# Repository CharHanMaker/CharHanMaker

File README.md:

# 🍚CharHan!!

チャーハンの調理を自動化するCharHan!!というロボットを作りました。

[CharHan!!-YouTube](https://www.youtube.com/watch?v=2m1POazWTIs)

## 🔥CharHan!!機械概要

案2を採用しました。

左右にモータを取り付けて左右の回転の同期する制御を入れています。

左右のリンクにエンコーダを搭載しており、角度と速度を左右で同期しています。

制御器は3種類設計し、評価しました。

## 🤖炒め作業の自動化

このようなチャーハンファームを作ることで省人化できるのではないかと思っております。

## 📁ファイルに関して

- Program
  - ロボットを動かすソフトウェアが入っています。PlatformIOで開発を行いました。
  - SystemIdentificationDataにMATLABでシステム同定を行ったプログラムが入っています。
    - 以下がシステム同定を行うために使用した組み込み側のデータロギングのプログラムです。シリアルモニターで受け取った文字列を元にCSVで書き出して整形してシステム同定を行いました。
    - `Program/main_tomix/src/Modes/SystemIdentification2`
    - `Program/main_tomix/src/Modes/SystemIdentification2`
- PCB
  - 基板データが入っています。KiCad7で開発しました。
- Image
  - README.mdの画像が入っています。

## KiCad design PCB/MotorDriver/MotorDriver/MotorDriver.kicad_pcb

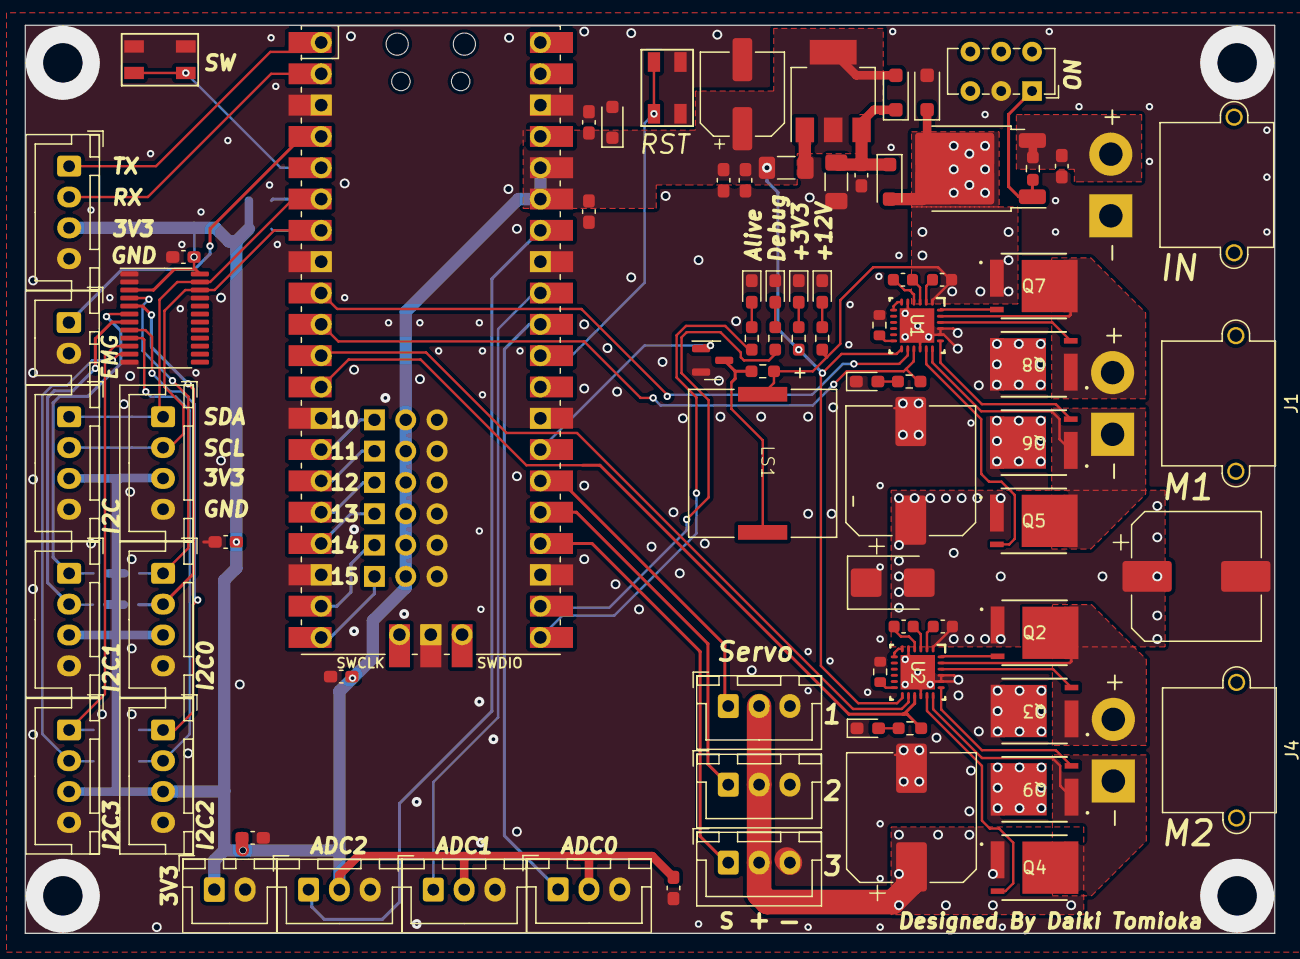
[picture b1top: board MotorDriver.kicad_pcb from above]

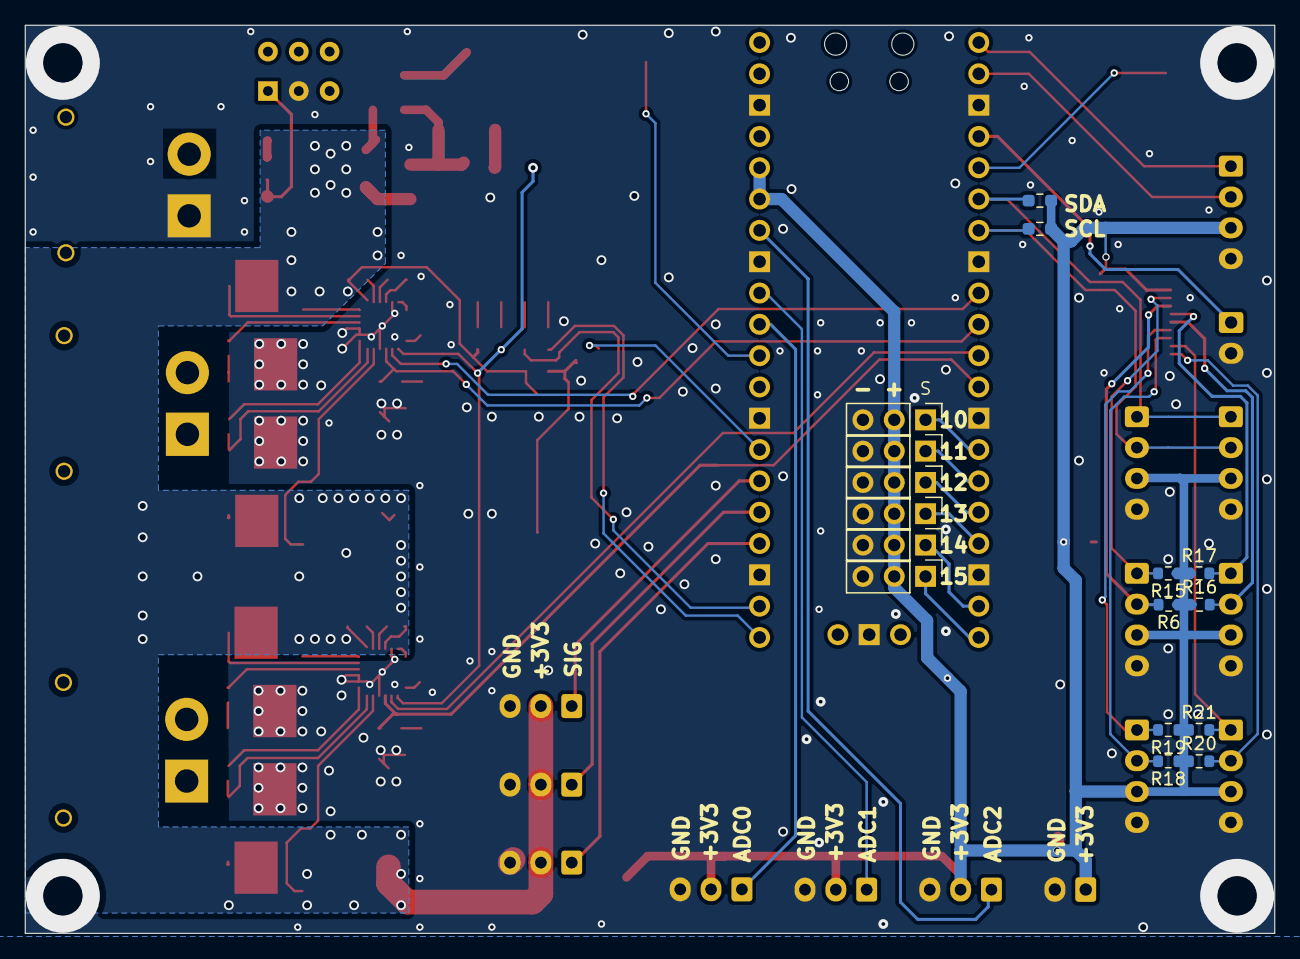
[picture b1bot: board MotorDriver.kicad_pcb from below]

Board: 2 copper layers, 101.3 x 73.7 mm, 95 parts (16 on the bottom side), 69 nets.

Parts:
C1, C17: 0.1u; C_0603_1608Metric
C2, C12: 1u; C_0603_1608Metric
C3, C11, C21: 220u; CP_Elec_10x10
C4, C5, C8, C9, C10, C13, C15, C16, C18, C19, C20: 0.1u; C_0603_1608Metric_Pad1.08x0.95mm_HandSolder
C6, C7: 22u; C_1206_3216Metric_Pad1.33x1.80mm_HandSolder
C14: 220u; CP_Elec_6.3x5.4
D1, D2, D10: ＧＳ１０１０ＦＬ; D_SOD-123F
D3: 3.3V; D_SOD-323_HandSoldering
D4, D5, D6, D7, D8, D9: LED; LED_0603_1608Metric_Pad1.05x0.95mm_HandSolder
J1, J3, J4: XT30PW-M; AMASS_XT30PW-M_1x02_P2.50mm_Horizontal
J2, J5, J9, J10, J13, J15: JST-XH; JST_XH_B3B-XH-A_1x03_P2.50mm_Vertical
J6, J24: JST-XH; JST_XH_B2B-XH-A_1x02_P2.50mm_Vertical
J7, J8, J11, J12, J14, J17, J18: JST-XH; JST_XH_B4B-XH-A_1x04_P2.50mm_Vertical
J16, J19, J20, J21, J22, J23: JST-XH; PinHeader_1x03_P2.54mm_Vertical
LS1: PKLCS1212E4001-R1; PKL
Q1: TJ60S04M3L; TO-252-2
Q2, Q3, Q4, Q5, Q6, Q7, Q8, Q9: NMOS; TPH11006NL_SOP Advance_TOS-M
Q10: NMOS; SOT-23
R1, R3: 10k; R_0603_1608Metric
R2, R5, R7, R8, R14: 10k; R_0603_1608Metric_Pad0.98x0.95mm_HandSolder
R6, R15, R16, R17, R18, R19, R20, R21: 4.7k; R_0603_1608Metric
R9, R10, R11, R12, R13: 1k; R_0603_1608Metric_Pad0.98x0.95mm_HandSolder
SW1: SW_DPST_x2; SW_E-Switch_EG1271_SPDT
SW2, SW3: SW_Push; SKRPACE010
TVS1: 12V; D_SMB
U1, U2: DRV8701ERGET; DRV8701ERGET_NV
U3: TCA9548APWR; TSSOP-24_4.4x7.8mm_P0.65mm
U4: Pico; RPi_Pico_SMD_TH
U5: AZ1117CH-3.3TR; SOT-223-3_TabPin2

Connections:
+3V3: C7.1, C8.1, C9.1, C10.1, C13.1, C14.1, C15.1, C16.1, C18.1, C19.1, C20.1, D3.1 (K), D10.2 (A), J7.3, J8.3, J10.2, J11.3, J12.3, J13.2, J14.3, J15.2, J16.2, J17.3, J18.3, J19.2, J20.2, J21.2, J22.2, J23.2, J24.1, R6.1, R7.1, R9.1, R14.1, R15.1, R16.1, R17.1, R18.1, R19.1, R20.1, R21.1, U1.13 (SLEEP_N), U2.13 (SLEEP_N), U3.3 (~RESET), U3.24 (VCC), U4.35 (ADC_VREF), U4.36 (3V3), U5.2 (OUTPUT)
+12V: C2.1, C3.1, C11.1, C12.1, C21.1, D1.2 (A), D2.1 (K), J2.2, J5.2, J9.2, LS1.P, Q1.2 (D), Q2.1 (D), Q4.1 (D), Q5.1 (D), Q7.1 (D), R5.1, R8.1, TVS1.2 (A), U1.1 (VM), U2.1 (VM)
+BATT: C4.2, J3.2, Q1.3 (S), R2.1
/12VIN: C5.1, C6.1, D1.1 (K), D10.1 (K), U5.3 (INPUT)
/MotorDriveUnit1/AVDD: U2.6 (VREF), U2.7 (AVDD)
/MotorDriveUnit/AVDD: U1.6 (VREF), U1.7 (AVDD)
ADC0: J10.1, U4.31 (GPIO26_ADC0)
ADC1: J13.1, U4.32 (GPIO27_ADC1)
ADC2: J15.1, U4.34 (GPIO28_ADC2)
Alive_LED: R13.1, U4.22 (GPIO17)
BUZZER: Q10.2 (G), U4.27 (GPIO21)
Debug_LED: R12.1, U4.21 (GPIO16)
EMG: J6.1, U4.4 (GPIO2)
GND: C3.2, C4.1, C5.2, C6.2, C7.2, C8.2, C9.2, C10.2, C11.2, C13.2, C14.2, C15.2, C16.2, C18.2, C19.2, C20.2, C21.2, D2.2 (A), D3.2 (A), D4.1 (K), D5.1 (K), D6.1 (K), D7.1 (K), D8.1 (K), D9.1 (K), J2.3, J3.1, J5.3, J6.2, J7.4, J8.4, J9.3, J10.3, J11.4, J12.4, J13.3, J14.4, J15.3, J16.3, J17.4, J18.4, J19.3, J20.3, J21.3, J22.3, J23.3, J24.2, Q3.3 (S), Q6.3 (S), Q8.3 (S), Q9.3 (S), Q10.3 (S), R1.1, R3.1, SW1.2 (B), SW2.1, SW3.1, TVS1.1 (K), U1.5 (GND), U1.16 (GND), U1.20 (SN), U1.21 (SP), U1.25 (PAD), U2.5 (GND), U2.16 (GND), U2.20 (SN), U2.21 (SP), U2.25 (PAD), U3.1 (A0), U3.2 (A1), U3.12 (GND), U3.21 (A2), U4.3 (GND), U4.8 (GND), U4.13 (GND), U4.18 (GND), U4.23 (GND), U4.28 (GND), U4.33 (AGND), U4.38 (GND), U4.42 (GND), U5.1 (GND)
GPIO10: J16.1, U4.14 (GPIO10)
GPIO11: J19.1, U4.15 (GPIO11)
GPIO12: J20.1, U4.16 (GPIO12)
GPIO13: J21.1, U4.17 (GPIO13)
GPIO14: J22.1, U4.19 (GPIO14)
GPIO15: J23.1, U4.20 (GPIO15)
INA1: R10.1, U1.15 (PH_IN1), U4.10 (GPIO7)
INA2: U1.14 (EN_IN2), U4.9 (GPIO6)
INB1: R11.1, U2.15 (PH_IN1), U4.12 (GPIO9)
INB2: U2.14 (EN_IN2), U4.11 (GPIO8)
Motor1A: J1.1, Q5.3 (S), Q6.1 (D), U1.18 (SH1)
Motor1B: J1.2, Q7.3 (S), Q8.1 (D), U1.23 (SH2)
Motor2A: J4.1, Q4.3 (S), Q9.1 (D), U2.18 (SH1)
Motor2B: J4.2, Q2.3 (S), Q3.1 (D), U2.23 (SH2)
unnamed: D4.2 (A), R8.2
unnamed: D5.2 (A), R9.2
unnamed: D6.2 (A), R10.2
unnamed: D7.2 (A), R11.2
unnamed: D8.2 (A), R12.2
unnamed: D9.2 (A), R13.2
unnamed: Q1.1 (G), R2.2, SW1.1 (A)
unnamed: Q2.2 (G), U2.24 (GH2)
unnamed: Q3.2 (G), U2.22 (GL2)
unnamed: Q4.2 (G), U2.17 (GH1)
unnamed: Q5.2 (G), U1.17 (GH1)
unnamed: Q6.2 (G), U1.19 (GL1)
unnamed: Q7.2 (G), U1.24 (GH2)
unnamed: Q8.2 (G), U1.22 (GL2)
unnamed: Q9.2 (G), U2.19 (GL1)
unnamed: LS1.N, Q10.1 (D), R5.2
unnamed: C1.1, U1.3 (CPH)
unnamed: C1.2, U1.4 (CPL)
unnamed: R1.2, U1.12 (IDRIVE)
unnamed: C2.2, U1.2 (VCP)
unnamed: C17.1, U2.3 (CPH)
unnamed: C17.2, U2.4 (CPL)
unnamed: R3.2, U2.12 (IDRIVE)
unnamed: C12.2, U2.2 (VCP)
RUN: SW3.2, U4.30 (RUN)
RX0: J17.2, U4.2 (GPIO1)
SCL: J8.2, J11.2, R14.2, U3.22 (SCL), U4.7 (GPIO5)
SCL0: J7.2, R6.2, U3.5 (SC0)
SCL1: J12.2, R16.2, U3.7 (SC1)
SCL2: J14.2, R18.2, U3.9 (SC2)
SCL3: J18.2, R20.2, U3.11 (SC3)
SDA: J8.1, J11.1, R7.2, U3.23 (SDA), U4.6 (GPIO4)
SDA0: J7.1, R15.2, U3.4 (SD0)
SDA1: J12.1, R17.2, U3.6 (SD1)
SDA2: J14.1, R19.2, U3.8 (SD2)
SDA3: J18.1, R21.2, U3.10 (SD3)
SW: SW2.2, U4.5 (GPIO3)
Servo1: J9.1, U4.24 (GPIO18)
Servo2: J2.1, U4.25 (GPIO19)
Servo3: J5.1, U4.26 (GPIO20)
TX0: J17.1, U4.1 (GPIO0)

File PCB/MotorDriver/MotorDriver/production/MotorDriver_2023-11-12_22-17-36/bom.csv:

Designator,Footprint,Quantity,Value,LCSC Part #
"C1, C10, C13, C15, C16, C17, C18, C19, C20, C4, C5, C8, C9",0603,13,0.1u,
"C11, C21, C3",CP_Elec_10x10,3,220u,
"C12, C2",0603,2,1u,
C14,CP_Elec_6.3x5.4,1,220u,
"C6, C7",1206,2,22u,
D1,D_SOD-123F,1,ＧＳ１０１０ＦＬ,
D3,D_SOD-323_HandSoldering,1,D_Schottky,
"D4, D5, D6, D7, D8, D9",0603,6,LED,
"J1, J3, J4",AMASS_XT30PW-M_1x02_P2.50mm_Horizontal,3,XT30PW-M,
"J10, J13, J15, J2, J5, J9",JST_XH_B3B-XH-A_1x03_P2.50mm_Vertical,6,JST-XH,
"J11, J12, J14, J17, J18, J7, J8",JST_XH_B4B-XH-A_1x04_P2.50mm_Vertical,7,JST-XH,
"J16, J19, J20, J21, J22, J23",PinHeader_1x03_P2.54mm_Vertical,6,JST-XH,
"J24, J6",JST_XH_B2B-XH-A_1x02_P2.50mm_Vertical,2,JST-XH,
LS1,PKL,1,PKLCS1212E4001-R1,
Q1,TO-252-2,1,TJ60S04M3L,
Q10,SOT-23,1,NMOS,
"Q2, Q3, Q4, Q5, Q6, Q7, Q8, Q9",TPH11006NL_SOP Advance_TOS-M,8,NMOS,
"R1, R14, R2, R3, R5, R7, R8",0603,7,10k,
"R10, R11, R12, R13, R9",0603,5,1k,
"R15, R16, R17, R18, R19, R20, R21, R6",0603,8,4.7k,
SW1,SW_E-Switch_EG1271_SPDT,1,SW_DPST_x2,
"SW2, SW3",SKRPACE010,2,SW_Push,
"U1, U2",DRV8701ERGET_NV,2,DRV8701ERGET,
U3,TSSOP-24_4.4x7.8mm_P0.65mm,1,TCA9548APWR,
U4,RPi_Pico_SMD_TH,1,Pico,
U5,SOT-223-3_TabPin2,1,AZ1117CH-3.3TR,

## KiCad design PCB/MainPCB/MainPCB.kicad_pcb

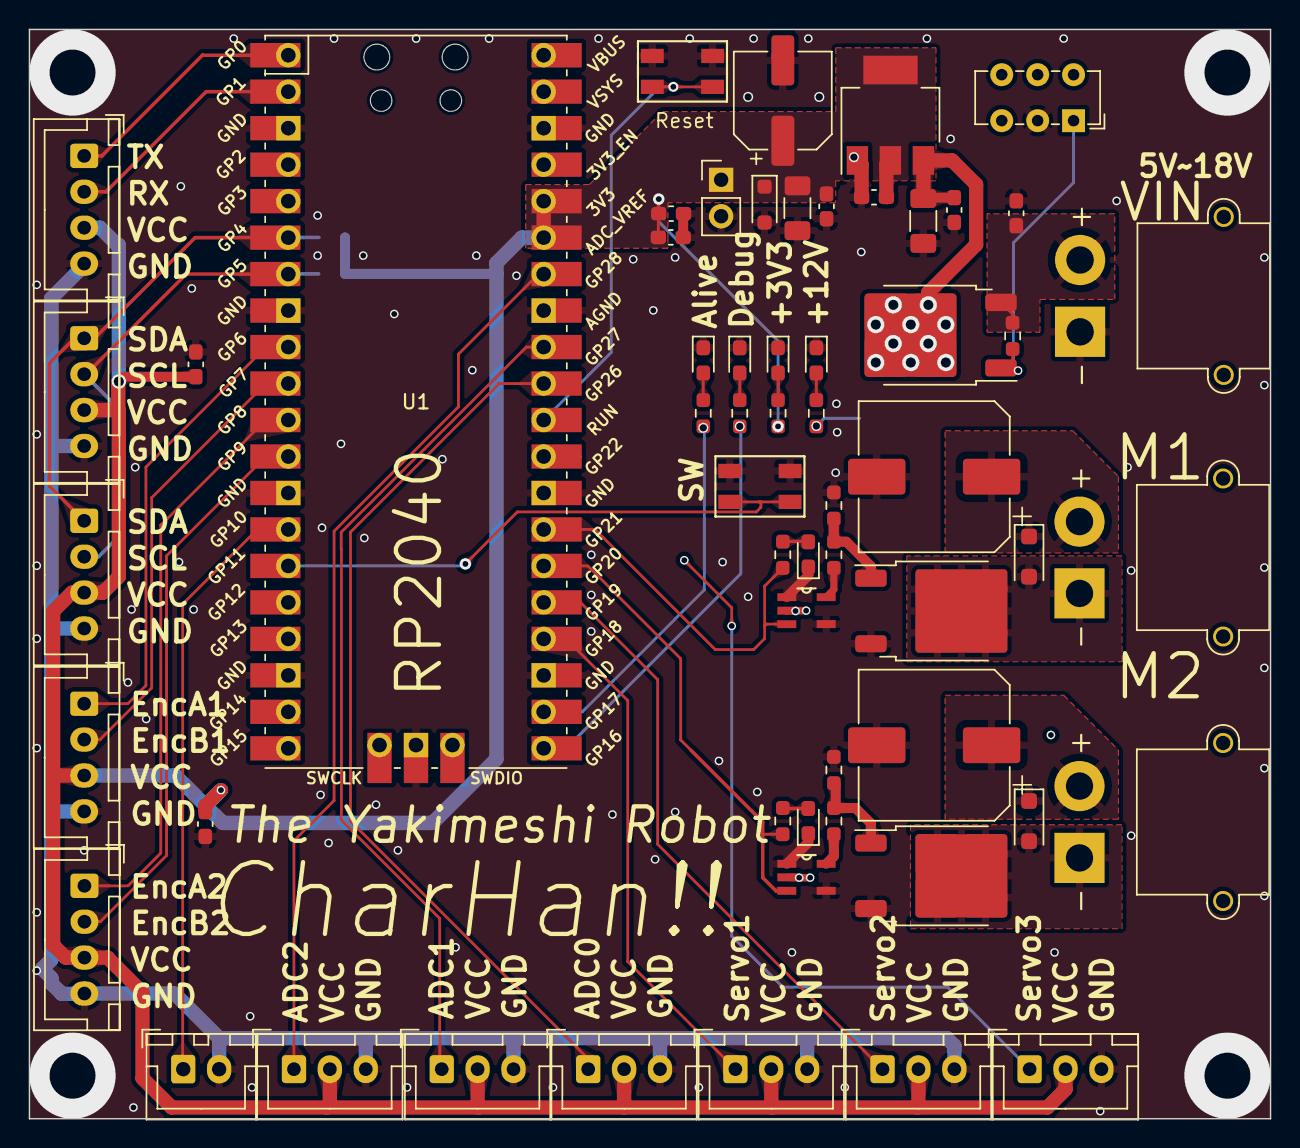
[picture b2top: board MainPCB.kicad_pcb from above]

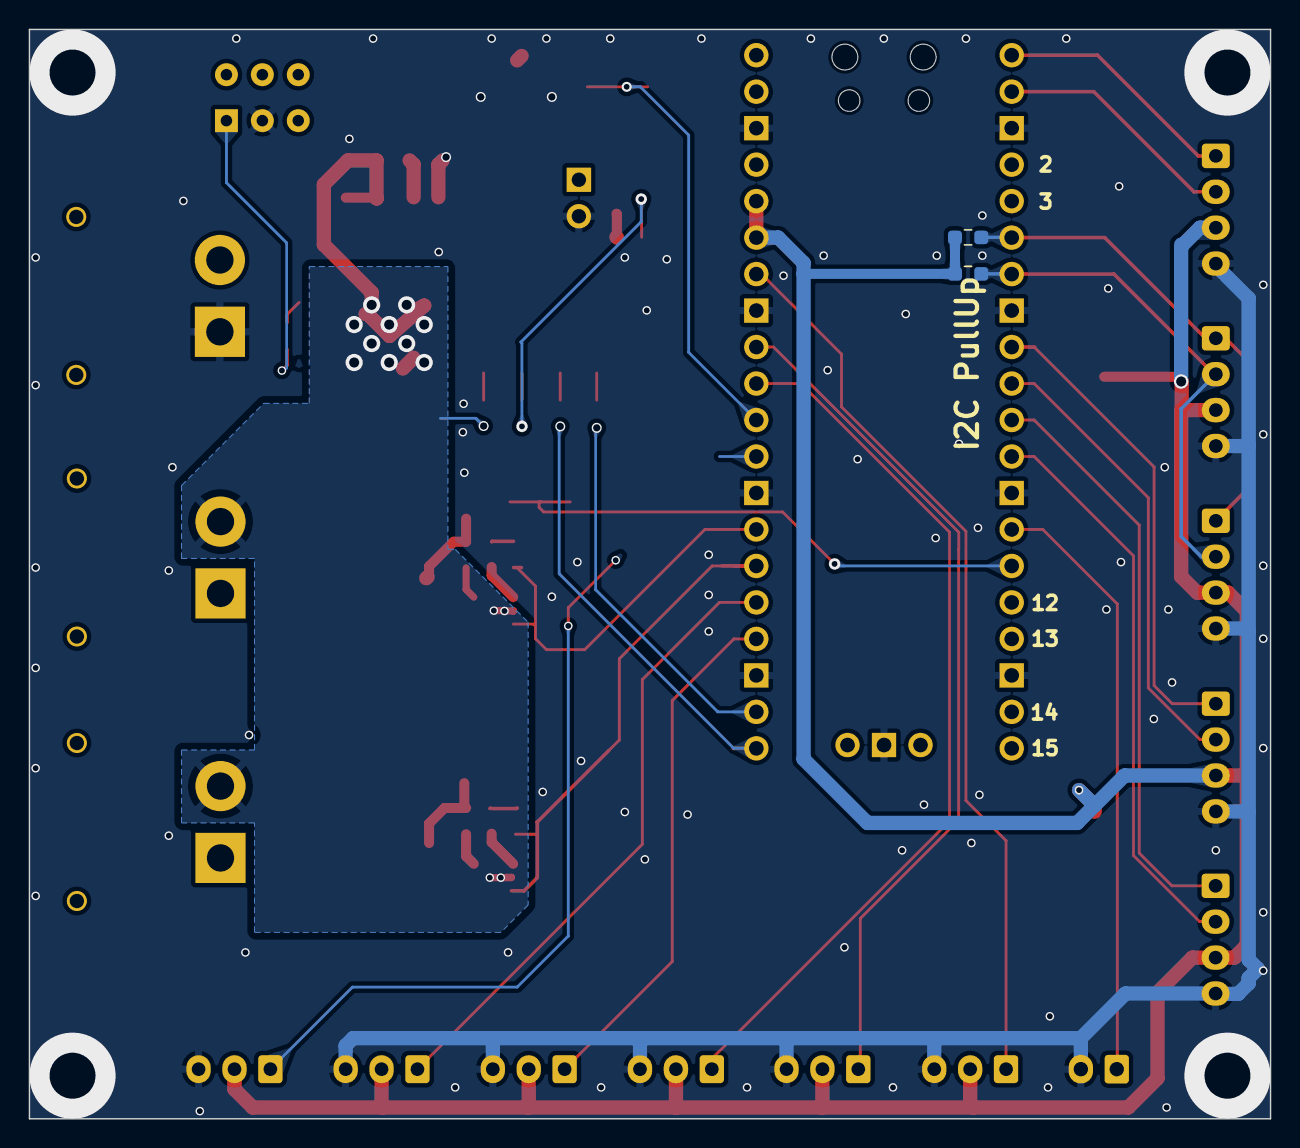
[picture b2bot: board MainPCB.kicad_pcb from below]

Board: 2 copper layers, 86.4 x 75.8 mm, 61 parts (2 on the bottom side), 38 nets.

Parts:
C2, C4: 220u; CP_Elec_10x10
C5, C6: 22u; C_1206_3216Metric_Pad1.33x1.80mm_HandSolder
C7, C9, C10, C11, C12, C13, C14, C15: 0.1u; C_0603_1608Metric_Pad1.08x0.95mm_HandSolder
C8: 220u; CP_Elec_6.3x5.4
D1: D_Schottky; D_SOD-323_HandSoldering
D2, D3, D4, D5, D6, D7: LED; LED_0603_1608Metric_Pad1.05x0.95mm_HandSolder
D8: ＧＳ１０１０ＦＬ; D_SOD-123F
D9: D; D_SOD-123F
J1, J12, J16: XT30PW-M; AMASS_XT30PW-M_1x02_P2.50mm_Horizontal
J2, J8, J9, J10, J11: JST-XH; JST_XH_B4B-XH-A_1x04_P2.50mm_Vertical
J3, J5, J6, J7, J14, J15: JST-XH; JST_XH_B3B-XH-A_1x03_P2.50mm_Vertical
J4: PinHeader_1x02_P2.54mm_Vertical
J13: JST-XH; JST_XH_B2B-XH-A_1x02_P2.50mm_Vertical
Q1, Q2: MTB7D0N6RJ3; TO-252-2
Q3: TJ60S04M3L; TO-252-2
R1, R2, R6, R7, R9: 1k; R_0603_1608Metric_Pad0.98x0.95mm_HandSolder
R3, R4, R5, R8, R10, R13: 10k; R_0603_1608Metric_Pad0.98x0.95mm_HandSolder
R11, R12: 51; R_0603_1608Metric_Pad0.98x0.95mm_HandSolder
SW1, SW3: SW_Push; SKRPACE010
SW2: SW_DPST_x2; SW_E-Switch_EG1271_SPDT
U1: Pico; RPi_Pico_SMD_TH
U2, U3: MCP1401T-E_OT; SOT95P270X145-5N
U4: AZ1117CH-3.3TR; SOT-223-3_TabPin2

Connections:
+3V3: C6.1, C7.1, C8.1, C9.1, C11.1, C12.1, C13.1, C14.1, D1.1 (K), J2.3, J3.2, J4.1, J5.2, J6.2, J7.2, J8.3, J9.3, J10.3, J11.3, J14.2, J15.2, R3.1, R4.1, R6.1, U1.35 (ADC_VREF), U1.36 (3V3), U4.2 (OUTPUT)
+12V: C2.1, C4.1, C5.1, C10.1, D8.1 (K), D9.1 (K), J1.2, J16.2, Q3.2 (D), R8.1, U2.2 (VDD), U3.2 (VDD), U4.3 (INPUT)
+BATT: C15.2, J12.2, Q3.3 (S), R5.1
ADC0: J5.1, U1.31 (GPIO26_ADC0)
ADC1: J6.1, U1.32 (GPIO27_ADC1)
ADC2: J7.1, U1.34 (GPIO28_ADC2)
Alive_LED: R9.1, U1.22 (GPIO17)
Debug_LED: R7.1, U1.21 (GPIO16)
EMG_SW: J13.1, U1.14 (GPIO10)
EncPortA1: J11.1, U1.9 (GPIO6)
EncPortA2: J10.1, U1.11 (GPIO8)
EncPortB1: J11.2, U1.10 (GPIO7)
EncPortB2: J10.2, U1.12 (GPIO9)
GND: C2.2, C4.2, C5.2, C6.2, C7.2, C8.2, C9.2, C10.2, C11.2, C12.2, C13.2, C14.2, C15.1, D1.2 (A), D2.1 (K), D3.1 (K), D4.1 (K), D5.1 (K), D6.1 (K), D7.1 (K), J2.4, J3.3, J4.2, J5.3, J6.3, J7.3, J8.4, J9.4, J10.4, J11.4, J12.1, J13.2, J14.3, J15.3, Q1.3 (S), Q2.3 (S), R10.2, R13.2, SW1.1, SW2.2 (B), SW3.1, U1.3 (GND), U1.8 (GND), U1.13 (GND), U1.18 (GND), U1.23 (GND), U1.28 (GND), U1.33 (AGND), U1.38 (GND), U1.42 (GND), U2.1 (GND), U2.4 (GND), U3.1 (GND), U3.4 (GND), U4.1 (GND)
MOut1: D9.2 (A), J16.1, Q2.2 (D)
MOut2: D8.2 (A), J1.1, Q1.2 (D)
MotorA: R1.1, U1.27 (GPIO21), U2.3 (IN)
MotorB: R2.1, U1.26 (GPIO20), U3.3 (IN)
unnamed: D2.2 (A), R8.2
unnamed: D3.2 (A), R6.2
unnamed: D4.2 (A), R7.2
unnamed: D5.2 (A), R9.2
unnamed: D6.2 (A), R1.2
unnamed: D7.2 (A), R2.2
unnamed: Q1.1 (G), R11.2, R13.1
unnamed: Q2.1 (G), R10.1, R12.2
unnamed: Q3.1 (G), R5.2, SW2.1 (A)
unnamed: R11.1, U2.5 (~OUT)
unnamed: R12.1, U3.5 (~OUT)
RUN: SW1.2, U1.30 (RUN)
RX0: J2.2, U1.2 (GPIO1)
SCL: J8.2, J9.2, R4.2, U1.7 (GPIO5)
SDA: J8.1, J9.1, R3.2, U1.6 (GPIO4)
SW: SW3.2, U1.15 (GPIO11)
Servo1: J14.1, U1.24 (GPIO18)
Servo2: J15.1, U1.25 (GPIO19)
Servo3: J3.1, U1.29 (GPIO22)
TX0: J2.1, U1.1 (GPIO0)

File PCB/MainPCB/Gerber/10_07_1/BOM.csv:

Comment,Designator,Footprint,JLCPCB Part #（optional）,
1k,"R2,R1,R6,R9,R7",R_0603_1608Metric_Pad0.98x0.95mm_HandSolder,,
LED,"D7,D6,D4,D2,D5,D3",LED_0603_1608Metric_Pad1.05x0.95mm_HandSolder,,
51,"R12,R11",R_0603_1608Metric_Pad0.98x0.95mm_HandSolder,,
10k,"R10,R8,R5",R_0603_1608Metric_Pad0.98x0.95mm_HandSolder,,
JST-XH,"J6,J7,J15,J5,J14,J3",JST_XH_B3B-XH-A_1x03_P2.50mm_Vertical,,
JST-XH,"J2,J8,J9,J11,J10",JST_XH_B4B-XH-A_1x04_P2.50mm_Vertical,,
330u,"C4,C2",CP_Elec_6.3x7.7,,
NMOS,"Q2,Q1",TO-252-2,,
0.1u,"C7,C3,C1,C9,C11",C_0603_1608Metric_Pad1.08x0.95mm_HandSolder,,
D_Schottky,D1,D_SOD-323_HandSoldering,,
Pico,U1,RPi_Pico_SMD_TH,,
XT30PW-M,"J16,J12,J1",AMASS_XT30PW-M_1x02_P2.50mm_Horizontal,,
PMOS,Q3,TO-252-2,,
0.1u,C10,C_1210_3225Metric_Pad1.33x2.70mm_HandSolder,,
MCP1401T-E_OT,"U3,U2",SOT95P270X145-5N,,
220u,C8,CP_Elec_6.3x5.4,,
22u,C6,C_0603_1608Metric_Pad1.08x0.95mm_HandSolder,,
10u,C5,C_1210_3225Metric_Pad1.33x2.70mm_HandSolder,,
SW_Push,SW1,SKRPACE010,,
AZ1117CH-3.3TR,U4,SOT-223-3_TabPin2,,
JST-XH,J13,JST_XH_B2B-XH-A_1x02_P2.50mm_Vertical,,
SW_DPST_x2,SW2,SW_E-Switch_EG1271_SPDT,,

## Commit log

2023-10-09 :sparkles: Add Exist Files
2023-10-09 :fire: Remove DS_Store
    # ==== Emojis ====
    # ✨ :sparkles: Add new feature
    # ✅ :white_check_mark: Update existing feature (not bug)
    # ⚠️ :warning: Fix bug/error
    # 🔥 :fire: Remove files or features
    # ✏️ :pencil2: Fix typos
2023-10-13 :sparkles: フリーホイールダイオードを追加
    # ==== Emojis ====
    # ✨ :sparkles: Add new feature
    # ✅ :white_check_mark: Update existing feature (not bug)
    # ⚠️ :warning: Fix bug/error
    # 🔥 :fire: Remove files or features
    # ✏️ :pencil2: Fix typos
2023-10-14 :sparkles: Add gitignore
    # ==== Emojis ====
    # ✨ :sparkles: Add new feature
    # ✅ :white_check_mark: Update existing feature (not bug)
    # ⚠️ :warning: Fix bug/error
    # 🔥 :fire: Remove files or features
    # ✏️ :pencil2: Fix typos
2023-10-14 :sparkles: ピン配置を追加
    # ==== Emojis ====
    # ✨ :sparkles: Add new feature
    # ✅ :white_check_mark: Update existing feature (not bug)
    # ⚠️ :warning: Fix bug/error
    # 🔥 :fire: Remove files or features
    # ✏️ :pencil2: Fix typos
2023-10-14 :sparkles: Add Math
    # ==== Emojis ====
    # ✨ :sparkles: Add new feature
    # ✅ :white_check_mark: Update existing feature (not bug)
    # ⚠️ :warning: Fix bug/error
    # 🔥 :fire: Remove files or features
    # ✏️ :pencil2: Fix typos
2023-10-16 :sparkles: ファイルをきれいきれいした
    # ==== Emojis ====
    # ✨ :sparkles: Add new feature
    # ✅ :white_check_mark: Update existing feature (not bug)
    # ⚠️ :warning: Fix bug/error
    # 🔥 :fire: Remove files or features
    # ✏️ :pencil2: Fix typos
2023-10-16 :sparkles: Add PCB Production files
    # ==== Emojis ====
    # ✨ :sparkles: Add new feature
    # ✅ :white_check_mark: Update existing feature (not bug)
    # ⚠️ :warning: Fix bug/error
    # 🔥 :fire: Remove files or features
    # ✏️ :pencil2: Fix typos
2023-10-16 :sparkles: change encorder lib to Outer
    # ==== Emojis ====
    # ✨ :sparkles: Add new feature
    # ✅ :white_check_mark: Update existing feature (not bug)
    # ⚠️ :warning: Fix bug/error
    # 🔥 :fire: Remove files or features
    # ✏️ :pencil2: Fix typos
2023-10-22 :sparkles: PCB In Production
    # ==== Emojis ====
    # ✨ :sparkles: Add new feature
    # ✅ :white_check_mark: Update existing feature (not bug)
    # ⚠️ :warning: Fix bug/error
    # 🔥 :fire: Remove files or features
    # ✏️ :pencil2: Fix typos
2023-10-22 :sparkles: TickTwoを使った処理を書いた
    # ==== Emojis ====
    # ✨ :sparkles: Add new feature
    # ✅ :white_check_mark: Update existing feature (not bug)
    # ⚠️ :warning: Fix bug/error
    # 🔥 :fire: Remove files or features
    # ✏️ :pencil2: Fix typos
2023-10-22 :sparkles: PICOのEEPROM(FLASH)の書き込みと読み出しのプログラムの検証成功
    # ==== Emojis ====
    # ✨ :sparkles: Add new feature
    # ✅ :white_check_mark: Update existing feature (not bug)
    # ⚠️ :warning: Fix bug/error
    # 🔥 :fire: Remove files or features
    # ✏️ :pencil2: Fix typos
2023-10-29 :sparkles: add MultipleAS5600 library
    # ==== Emojis ====
    # ✨ :sparkles: Add new feature
    # ✅ :white_check_mark: Update existing feature (not bug)
    # ⚠️ :warning: Fix bug/error
    # 🔥 :fire: Remove files or features
    # ✏️ :pencil2: Fix typos
2023-10-29 :sparkles: anglerVelocityが取得可能に
    # ==== Emojis ====
    # ✨ :sparkles: Add new feature
    # ✅ :white_check_mark: Update existing feature (not bug)
    # ⚠️ :warning: Fix bug/error
    # 🔥 :fire: Remove files or features
    # ✏️ :pencil2: Fix typos
2023-10-29 :sparkles: Mode管理が可能になりました
    loopの中で変数が維持されているのを観測した．
    using Devices::Devices;が肝．C++11の機能．継承コンストラクタ
    https://cpprefjp.github.io/lang/cpp11/inheriting_constructors.html
2023-10-30 :sparkles: モード切り替えに対応した
    # ==== Emojis ====
    # ✨ :sparkles: Add new feature
    # ✅ :white_check_mark: Update existing feature (not bug)
    # ⚠️ :warning: Fix bug/error
    # 🔥 :fire: Remove files or features
    # ✏️ :pencil2: Fix typos
2023-10-31 :sparkles: GPIO設定ができた
    # ==== Emojis ====
    # ✨ :sparkles: Add new feature
    # ✅ :white_check_mark: Update existing feature (not bug)
    # ⚠️ :warning: Fix bug/error
    # 🔥 :fire: Remove files or features
    # ✏️ :pencil2: Fix typos
2023-11-01 :sparkles: モータ端子間電圧が飽和しないPWM周波数が決定した
    # ==== Emojis ====
    # ✨ :sparkles: Add new feature
    # ✅ :white_check_mark: Update existing feature (not bug)
    # ⚠️ :warning: Fix bug/error
    # 🔥 :fire: Remove files or features
    # ✏️ :pencil2: Fix typos
2023-11-01 :sparkles: システム同定ようのソースコード
    # ==== Emojis ====
    # ✨ :sparkles: Add new feature
    # ✅ :white_check_mark: Update existing feature (not bug)
    # ⚠️ :warning: Fix bug/error
    # 🔥 :fire: Remove files or features
    # ✏️ :pencil2: Fix typos
2023-11-02 :sparkles: モード追加スクリプトCreateMode.pyを追加
    # ==== Emojis ====
    # ✨ :sparkles: Add new feature
    # ✅ :white_check_mark: Update existing feature (not bug)
    # ⚠️ :warning: Fix bug/error
    # 🔥 :fire: Remove files or features
    # ✏️ :pencil2: Fix typos
2023-11-06 :sparkles: MDを作り始めた
    # ==== Emojis ====
    # ✨ :sparkles: Add new feature
    # ✅ :white_check_mark: Update existing feature (not bug)
    # ⚠️ :warning: Fix bug/error
    # 🔥 :fire: Remove files or features
    # ✏️ :pencil2: Fix typos
2023-11-06 システム同定用のライブラリを書いた
2023-11-06 :sparkles: システム同定用プログラムの更新
    # ==== Emojis ====
    # ✨ :sparkles: Add new feature
    # ✅ :white_check_mark: Update existing feature (not bug)
    # ⚠️ :warning: Fix bug/error
    # 🔥 :fire: Remove files or features
    # ✏️ :pencil2: Fix typos
2023-11-06 :sparkles: システム同定に必要なデータを取得できた！
    # 問題発生
    なぜなのか！？0番目のエンコーダの角度を取得しないと1番目のエンコーダの角度が取得できないｗｗｗｗｗｗｗｗｗｗｗｗ
    theta = AbsEncorders.readDegree(0);
    AbsEncorders.readDegree(1);
    omega = AbsEncorders.getVelocity(0);
2023-11-07 :sparkles: システム同定用のデータを取得したよ
    # ==== Emojis ====
    # ✨ :sparkles: Add new feature
    # ✅ :white_check_mark: Update existing feature (not bug)
    # ⚠️ :warning: Fix bug/error
    # 🔥 :fire: Remove files or features
    # ✏️ :pencil2: Fix typos
2023-11-07 :sparkles: システム同定用データを追加した
    10KHzで4回とって平均データを追加した．
2023-11-07 :sparkles: 可制御域だけのデータを追加した
    # ==== Emojis ====
    # ✨ :sparkles: Add new feature
    # ✅ :white_check_mark: Update existing feature (not bug)
    # ⚠️ :warning: Fix bug/error
    # 🔥 :fire: Remove files or features
    # ✏️ :pencil2: Fix typos
2023-11-07 matlabで伝達関数を求めた 画像も取った
2023-11-08 :sparkles: 一次遅れのステップ応答をSimulinkで作れた
    # ==== Emojis ====
    # ✨ :sparkles: Add new feature
    # ✅ :white_check_mark: Update existing feature (not bug)
    # ⚠️ :warning: Fix bug/error
    # 🔥 :fire: Remove files or features
    # ✏️ :pencil2: Fix typos
2023-11-08 伝達関数を使ったブロック線図を作った
2023-11-08 :pencil2: update gitignore
    # ==== Emojis ====
    # ✨ :sparkles: Add new feature
    # ✅ :white_check_mark: Update existing feature (not bug)
    # ⚠️ :warning: Fix bug/error
    # 🔥 :fire: Remove files or features
    # ✏️ :pencil2: Fix typos
2023-11-08 ilaplace した
2023-11-08 PIDを用いた、目標角速度に追従するプログラム ただし、ゲインは未設定
2023-11-08 :sparkles: タイマー割り込みでLチカした
    - 今回使ったのは https://github.com/khoih-prog/RPI_PICO_TimerInterrupt というライブラリ
    - public archiveになっているので，よくわからない．使えなくなるかもしれない．
2023-11-10 入力電圧を-1倍するのを書き加えた
2023-11-11 :sparkles: 基板V2完成！！！
    MotorDriverになってるけど普通にMain PCB V2ですわ！
2023-11-11 :sparkles: ビアの追加
2023-11-11 :sparklesビアの追加
2023-11-11 Revert ":sparkles: ビアの追加"
    This reverts commit f41483c75bcc19d71434e040f06f5bb4b5903eec.
2023-11-11 1周期ごとに周波数を2倍していく入力プログラムを作った
2023-11-12 :sparkles: 基板の穴の位置とビアの修正
2023-11-12 :sparkles: PCB Production DONE!!
2023-11-13 MATLABでもういくつか伝達関数を同定した
2023-11-13 PIDライブラリを修正した
2023-11-13 ステップ応答でシステム同定を試みる
2023-11-14 matlabのsystem identificationで伝達関数増やした
2023-11-14 一応カスケードのブロック線図を描いた
2023-11-14 Big FIX on Encoder
    - degree から radians
    - 正転と逆転
    - 初期位置を確保できるように(偏差を出力)
2023-11-22 シミュのブロック線図を作ってモータコントロールのcppをたてた
2023-11-22 ControlMotorModeをちょっと進めた
2023-11-23 エンコーダが出す値の単位がradとrad/sになったはず。詳しく確認したい
2023-11-23 :sparkles: Production Done
2023-11-29 角度同期のプログラムを書いてる途中
2023-11-29 変数を配列で管理するようにした
2023-11-29 モータ回った！
2023-11-29 set pinName
2023-11-29 LAP制御ができた
    次はSMPしたい
2023-11-29 SMP制御ができた！
2023-11-29 :sparkles: 速度PID制御の雛形ができたよ
2023-11-29 :sparkles: 新チャーハン基板でエンコーダが読めたことが確認できた
    # 注意
    「以下のように2つ以上のエンコーダを読もうとしないとエンコーダを読むことができない仕様があります．」と思っていたら，何故か単体でも動いたわなんでやw
    ↓↓コレネ↓↓
    float angle0 = AbsEncorders.readDegree(0);
    float angle1 = AbsEncorders.readDegree(1);
    float vel0 = AbsEncorders.getVelocity(0);
2023-12-01 ⚠️ エンコーダの単位とコメントを修正した(つもり)
    怪しいところいっぱいある
2023-12-01 ✨ 連続角度がでるはずなプログラムを書いたWIP
    @ryoskRFR チェックプリーズ!
2023-12-01 進捗セーブ
2023-12-01 ✨ 連続角度がでるはずなプログラムを書いた(はず)
2023-12-04 ✏️ エンコーダの根本的なリファクタリングなう
    - raw12Bitデータを読み取るやつ
2023-12-04 ✏️ 連続角度とread12BitValueと角速度のリファクタ
2023-12-05 ✏️ 回転回数の向きをisCWに基づいて行うように変更
2023-12-06 ✨ エンコーダ関連完全に動きました
    - readRawValue
    - read12BitValue
    - readDegree
    - readRadians
    - getVelocity
    - getContinuousDegree
2023-12-06 MotorPID をつくった
2023-12-06 PIDのファイルを作った
2023-12-06 ✨ 起動音が鳴るようになった
2023-12-06 ✨ モード切り替えで音が鳴るようになった
2023-12-06 クラスの継承がうまくいった。
2023-12-06 ✏️ MotorAが回転することを確認
2023-12-07 ✨ MotorB動きました
2023-12-07 申し訳程度の同期と加速->定速テスター
2023-12-07 目標角速度と目標角を書くコードを書けたはず(お気持ち)。立ち上がってから角に誤差があるはず。
2023-12-08 warningをなくした
2023-12-08 だいきが更新した磁気エンコーダライブラリを組み込んだ
2023-12-08 いらないところをトリミング
2023-12-08 mainからControlMotorModeを使えるようにした。
2023-12-08 rotationCountに関するerrorを修正
2023-12-08 モータの立ち上がりの際のpwm増加量とか修正した
2023-12-08 ✏️エンコーダライブラリの修正
2023-12-08 ✨センサのテストモードを追加
2023-12-08 ✨ 音色を追加
2023-12-08 ✨ブザーから音を出す部分を修正
2023-12-08 ✏️エンコーダの初期位置を任意の値にできるように変更した
2023-12-08 ✨ EEPROMにエンコーダの値を読み書きできるように実装した
2023-12-08 ✏️ コメント追加
2023-12-08 ✨ SensorTest内でエンコーダのZeroPosを書き込む際に、エンコーダが接続されていないとアラームを出すようにした
2023-12-08 ✨ MainModeで初期角度をbeforeでEEPROMから読み込むようにした
    これはそれぞれのbeforeで読み込まないと設計上ちゃんと動作しないです(ロボットの起動時に読み込もうとしたが失敗した)
2023-12-08 ✨ EEPROMに書き込んだら再起動するようにした
2023-12-09 ✏️ Fix gitignore to ignore .vscode/
2023-12-09 ✨ add MotorVelTest
2023-12-10 ✨ 速度制御みたいなことができた！！
2023-12-10 ✏️ PIDのライブラリを編集した(resetIntegral)
2023-12-11 ✏️ [PCB] モータからの逆起電力対策ダイオードを追加
2023-12-12 ✏️ 速度PIDゲイン変更
2023-12-12 ✨ 新しいMDでシステム同定した
2023-12-12 ✏️ 連続角度が連続していなかったので修正
2023-12-12 速度制御，PI制御よりもI制御の方が安定しているんだが？？
2023-12-12 ✏️ センサーテストの時にEEPROMから読み込むようにした
2023-12-12 MATLAB上の伝達関数を更新
2023-12-12 伝達関数を更新した
2023-12-13 立ち上がり中の目標値設定を修正した
2023-12-13 simulinkのブロック線図を更新した
2023-12-14 ✏️ 昔のファイルを引っ張てきた
2023-12-14 ✏️ 回路図を修正
2023-12-19 ２モータの角をPIDで同期させる（ゲイン未設定）
2023-12-20 変数の型とか目標角速度周りを修正
2023-12-20 モータ同期をテストする用のhppを作った（未検証）
2023-12-20 ✨基板をサージに強くした
    - TVSをサージ発生源に近くした
    - 12Vツェナーダイオードをレギュレータの近くに取り付けた
2023-12-20 ✨ モータの制御に逆起電力対策をした
2023-12-20 0Vで回る
2023-12-20 ✨ 新しくMotorAngleTestを生やした
    現状中身は左右の速度制御(同期なし)
2023-12-21 ✨ ゲインなどの変数の定義の仕方を変更
2023-12-21 ✨ 0度に向かってモータを動かす角度PIDみたいなやつをやり始めた
    ゲインは激ヤバなので注意
2023-12-21 ✨ 位置制御成功した(マスタースレーブ)
2023-12-22 motor[0]がおかしい
2023-12-22 saturation見直し、encoderのcontinuousRadがうまくいってない？
2023-12-22 constrainは使えたけど、deviceBeginはダメみたい
2023-12-22 simulationのゲインじゃ太刀打ちできん
2023-12-23 ✨無理矢理同期っぽいことした
2023-12-23 ✏️ エンコーダの連続角度のバグを修正
2023-12-23 2モータのシステム同期用のデータを取れるようにした
2023-12-23 ✨システム同定データ追加
2023-12-23 ✨AngleTestで最初の0ポジションに合わせるやつをリライトした
2023-12-24 ゲイン変えて、シンクロテストも改変した
2023-12-24 同期がうまくいってる
2023-12-24 擬似2自由度制御だと良い同期になる
2023-12-24 擬似2自由度制御のブロック線図を描いた
2023-12-25 ブロック線図を描きなおした
2023-12-26 ブロック線図を増やして、加筆修正した
2023-12-30 simulationのデータをplotした
2024-01-02 ブロック線図とグラフを訂正した
2024-01-02 凡例とか修正した
2024-01-08 グラフの軸範囲を変更
2024-01-09 速度+同期制御のデータを取り直した
2024-09-11 ✨READMEを更新
2024-09-11 ✨READMEを修正
